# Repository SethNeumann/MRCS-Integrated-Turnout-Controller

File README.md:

# REPO NAME: Integrated turnout Controller
## License: Creative Commons Attribution-NonCommercial-ShareAlike

The Integrated Turnout Controller (ITC) is designed to provide all control functions needed for remote, local, and locking of a turnout for various styles of turnout motors. The ITC provides LED outputs with onboard current limiting resistors for route and switch lock status.

The ITC can operate as a standalone turnout controller, with no computer needed. When connected to a computer for remote turnout control and the computer is not running, the ITC comes up in local mode. This allows for turnouts to be thrown manually using the Local input.

The (ITC) is an updated design of the MRCS Remote Stall Motor Controller (RSMC) introduced in 2013.

The ITC has the following features:

   - Standalone or computer turnout motor control
   - Local Throw input
   - Remote Throw input
   - Switch Lock input
   - Turnout position feedback output
   - Route LED ports, Normal/Reverse (Common Anode, Sinking)
   - Open Source sketch software
   - Motor power input, 9-12 Vdc
   - Onboard 5v regulator for logic power
   - Turnout motor driver (TC4428 MOSFET), up to 500 ma drive
   - Frog power routing using external switch contacts (Tortoise, Switchmaster™, MP1/MP5)
   - 8 position motor pads for a .156" Molex connector, .156" edge connector, or .100" (2.54mm)
   - Separate motor pads for connection to additional crossover turnout motors

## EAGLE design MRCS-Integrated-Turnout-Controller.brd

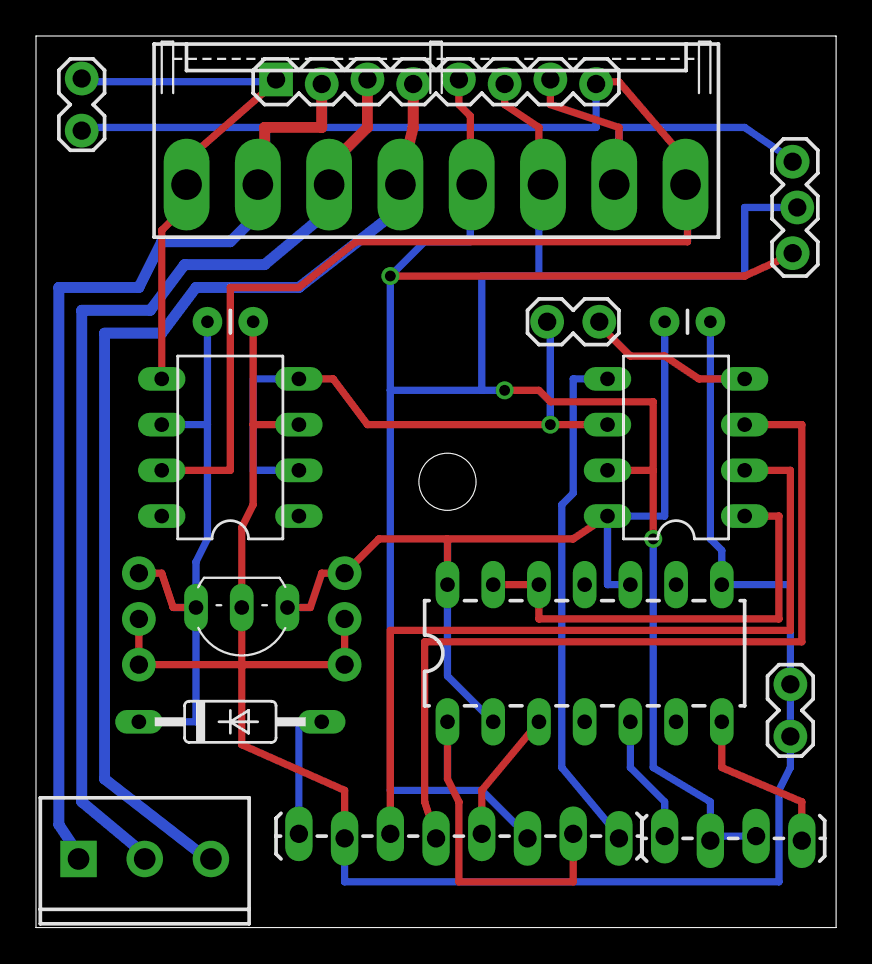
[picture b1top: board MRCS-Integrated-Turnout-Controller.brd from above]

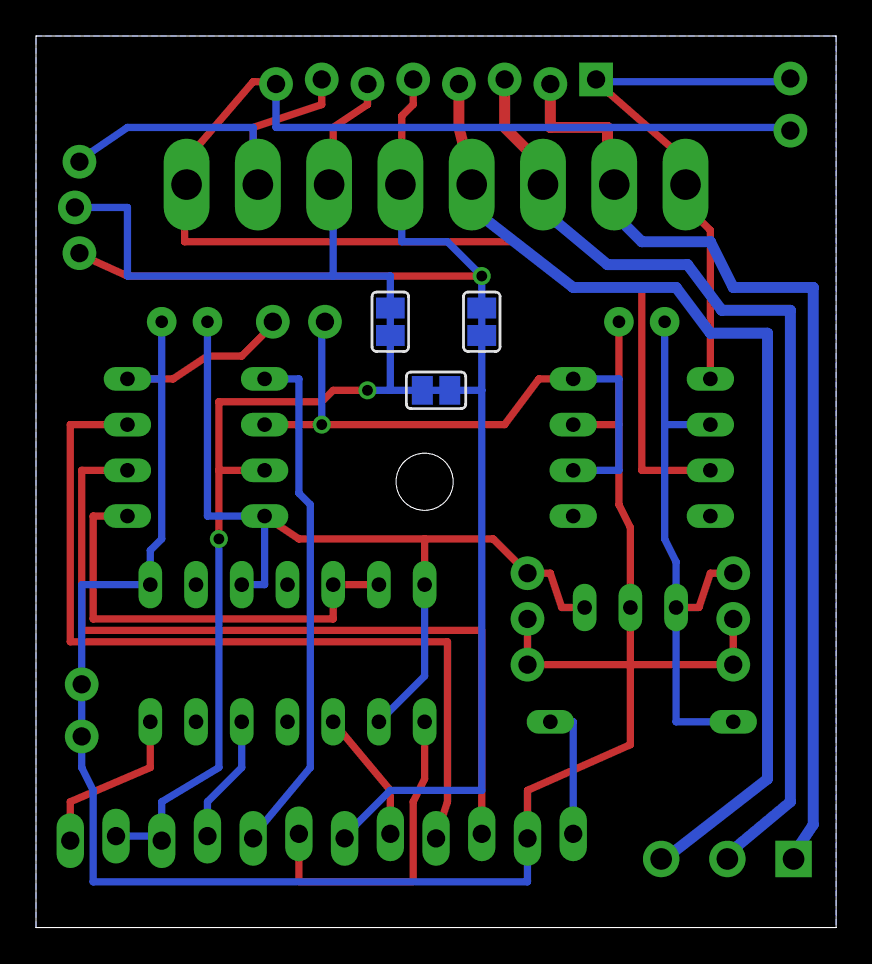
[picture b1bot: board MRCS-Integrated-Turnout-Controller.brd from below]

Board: 2 copper layers, 44.5 x 49.5 mm, 24 parts (3 on the bottom side), 3 nets.

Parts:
ACTPOS: SJ
C4: .01uf; CAP-PTH-SMALL
E$1: 1X08_LOCK
E$2: DRILL_0.1250
E$3: CAP-PTH-SMALL
E$4: C2992
E$5: CA-PROP65WARNING
E$6, E$18: 1X03_NO_SILK
E$7: MRCSLOGOTOP
E$8, E$11, E$13: 1X02_LOCK
E$9: 1X08_LOCK_LONGPADS
E$10: 1X04_LOCK_LONGPADS
E$12: 1X03_LOCK
FROG: SCREWTERMINAL-3.5MM-3_LOCK.007S
J1: KK-156-8-F
RN1: 1K; DIL14
T5, T6: SJ
U1: TC4428A; DIL08
U2: Tiny85; DIL08
U3: U3; TO92-BCE

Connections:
S$3: U1.4, U2.6
S$7: E$3.2, U1.3
S$29: C4.2, RN1.10, U2.8, U3.B

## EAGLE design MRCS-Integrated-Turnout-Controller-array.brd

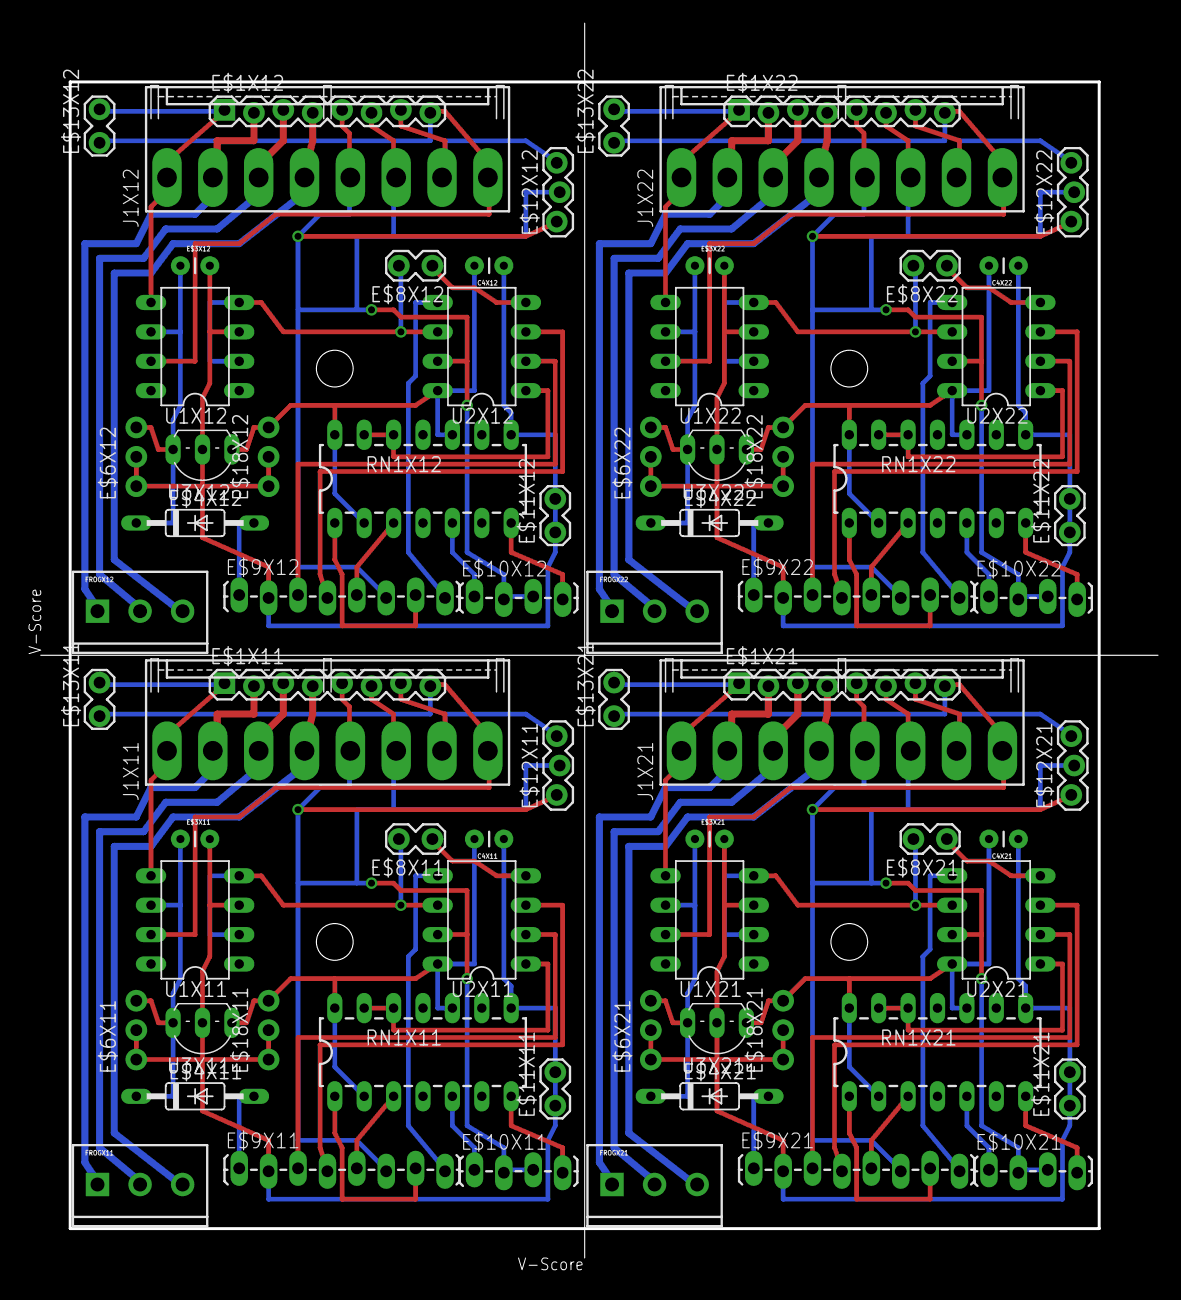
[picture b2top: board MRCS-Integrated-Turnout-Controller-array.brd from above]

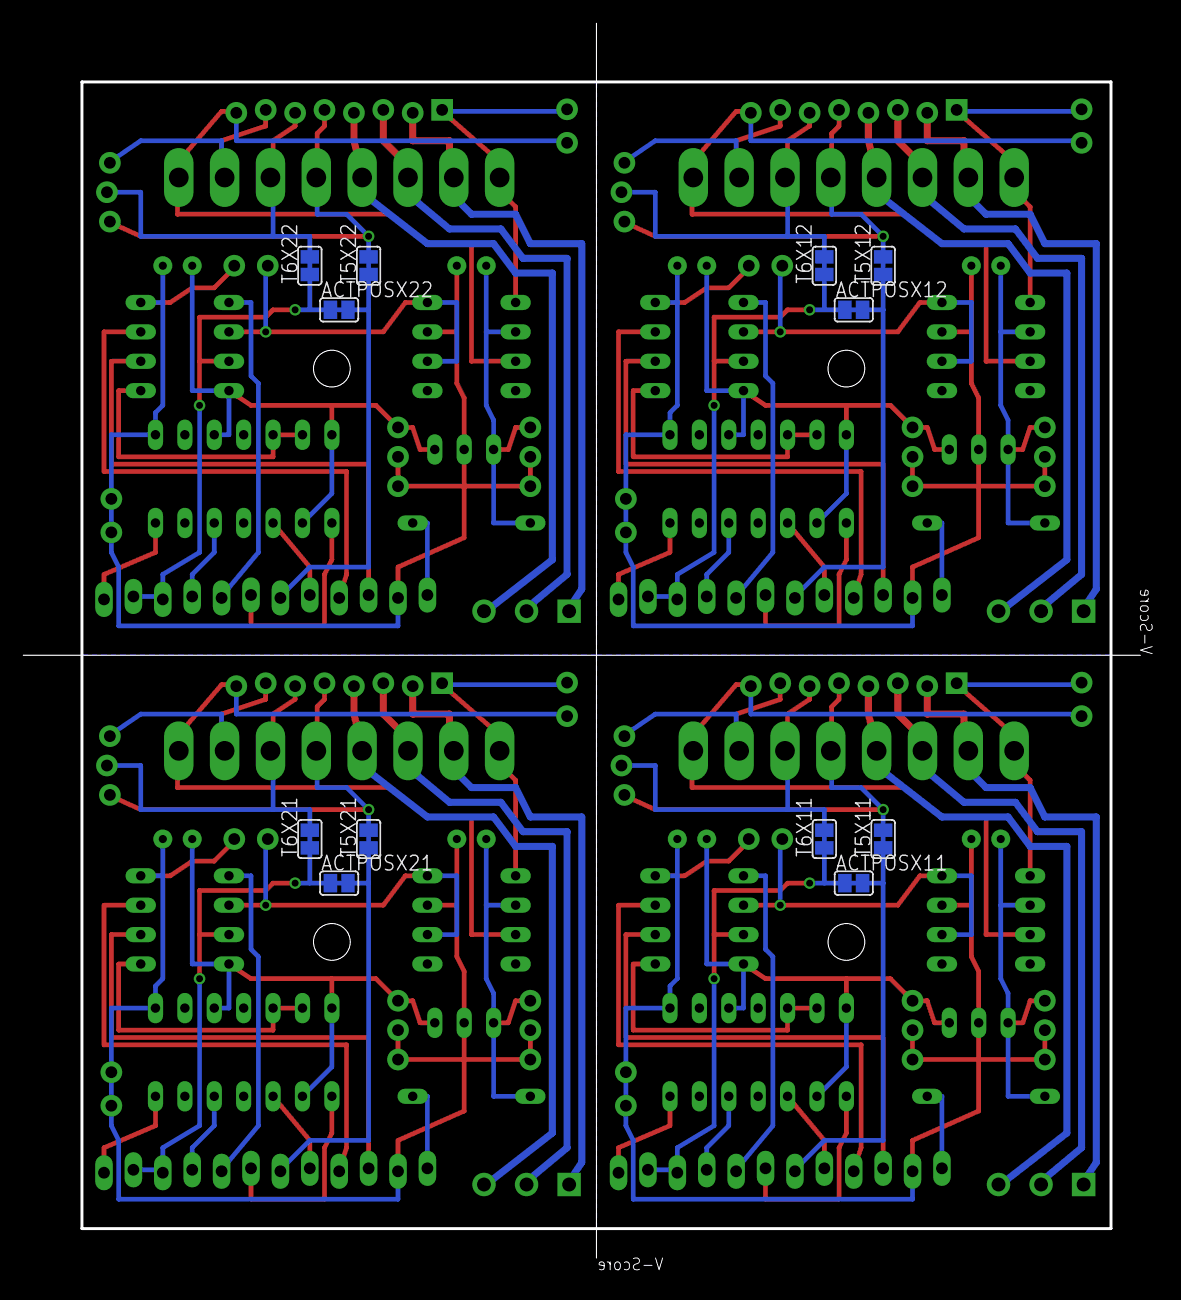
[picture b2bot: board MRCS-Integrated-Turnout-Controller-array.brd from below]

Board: 2 copper layers, 97.8 x 108.1 mm, 96 parts (12 on the bottom side), 12 nets.

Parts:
ACTPOSX11, ACTPOSX12, ACTPOSX21, ACTPOSX22: SJ
C4X11, C4X12, C4X21, C4X22: .01uf; CAP-PTH-SMALL
E$1X11, E$1X12, E$1X21, E$1X22: 1X08_LOCK
E$2X11, E$2X12, E$2X21, E$2X22: DRILL_0.1250
E$3X11, E$3X12, E$3X21, E$3X22: CAP-PTH-SMALL
E$4X11, E$4X12, E$4X21, E$4X22: C2992
E$5X11, E$5X12, E$5X21, E$5X22: CA-PROP65WARNING
E$6X11, E$6X12, E$6X21, E$6X22, E$18X11, E$18X12, E$18X21, E$18X22: 1X03_NO_SILK
E$7X11, E$7X12, E$7X21, E$7X22: MRCSLOGOTOP
E$8X11, E$8X12, E$8X21, E$8X22, E$11X11, E$11X12, E$11X21, E$11X22, E$13X11, E$13X12, E$13X21, E$13X22: 1X02_LOCK
E$9X11, E$9X12, E$9X21, E$9X22: 1X08_LOCK_LONGPADS
E$10X11, E$10X12, E$10X21, E$10X22: 1X04_LOCK_LONGPADS
E$12X11, E$12X12, E$12X21, E$12X22: 1X03_LOCK
FROGX11, FROGX12, FROGX21, FROGX22: SCREWTERMINAL-3.5MM-3_LOCK.007S
J1X11, J1X12, J1X21, J1X22: KK-156-8-F
RN1X11, RN1X12, RN1X21, RN1X22: 1K; DIL14
T5X11, T5X12, T5X21, T5X22, T6X11, T6X12, T6X21, T6X22: SJ
U1X11, U1X12, U1X21, U1X22: TC4428A; DIL08
U2X11, U2X12, U2X21, U2X22: Tiny85; DIL08
U3X11, U3X12, U3X21, U3X22: U3; TO92-BCE

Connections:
S$3X11: U1X11.4, U2X11.6
S$3X12: U1X12.4, U2X12.6
S$3X21: U1X21.4, U2X21.6
S$3X22: U1X22.4, U2X22.6
S$7X11: E$3X11.2, U1X11.3
S$7X12: E$3X12.2, U1X12.3
S$7X21: E$3X21.2, U1X21.3
S$7X22: E$3X22.2, U1X22.3
S$29X11: C4X11.2, RN1X11.10, U2X11.8, U3X11.B
S$29X12: C4X12.2, RN1X12.10, U2X12.8, U3X12.B
S$29X21: C4X21.2, RN1X21.10, U2X21.8, U3X21.B
S$29X22: C4X22.2, RN1X22.10, U2X22.8, U3X22.B

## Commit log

2020-08-10 Update INFO
2020-08-10 clean up documentation
    change Intelligent to Integrated
2020-12-20 documentation pdf
    some updates - needs more
2021-01-24 Changes to correct U1/U2 reversal on board labels
    silk changes

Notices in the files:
parts and their libraries:
SparkFun-Passives: Licensing: CC v3.0 Share-Alike You are welcome to use this library for commercial purposes.
